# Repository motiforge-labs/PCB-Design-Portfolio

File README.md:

# PCB Design Portfolio – Fawaz

A collection of custom PCB projects designed in KiCad.

## Projects

* 🌈 RGB Mood Light PCB
* 🌤 ESP32 OLED Weather / System Display PCB
* ⌨️ ESP32 Macro Pad Pro PCB

Each project folder contains:

* KiCad source files
* PCB screenshots
* 3D renders
* Project documentation (PDF)

## 🌈 RGB Mood Light PCB

## 🌤 ESP32 OLED Weather Display PCB

## ⌨️ ESP32 Macro Pad Pro PCB

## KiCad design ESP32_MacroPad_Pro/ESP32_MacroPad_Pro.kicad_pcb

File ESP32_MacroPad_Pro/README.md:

## ⌨️ ESP32 Macro Pad Pro PCB

A compact 6-key programmable macro pad built around the Arduino Nano ESP32. The design integrates WS2812B RGB LEDs for per-key lighting, a 0.91-inch I²C OLED display for status and menu information, USB-C connectivity, and a dedicated reset button. The PCB was designed in KiCad with a focus on clean component placement, efficient routing, dual-layer ground planes, and successful ERC/DRC verification.

**Features**
- Arduino Nano ESP32
- 6 Mechanical Key Switches
- 6 × WS2812B RGB LEDs
- 0.91-inch I²C OLED Display
- USB-C Connectivity
- Dual-Layer PCB
- ERC: 0 Errors, 0 Warnings
- DRC: 0 Errors, 0 Warnings

## ⌨️ ESP32 Macro Pad Pro PCB

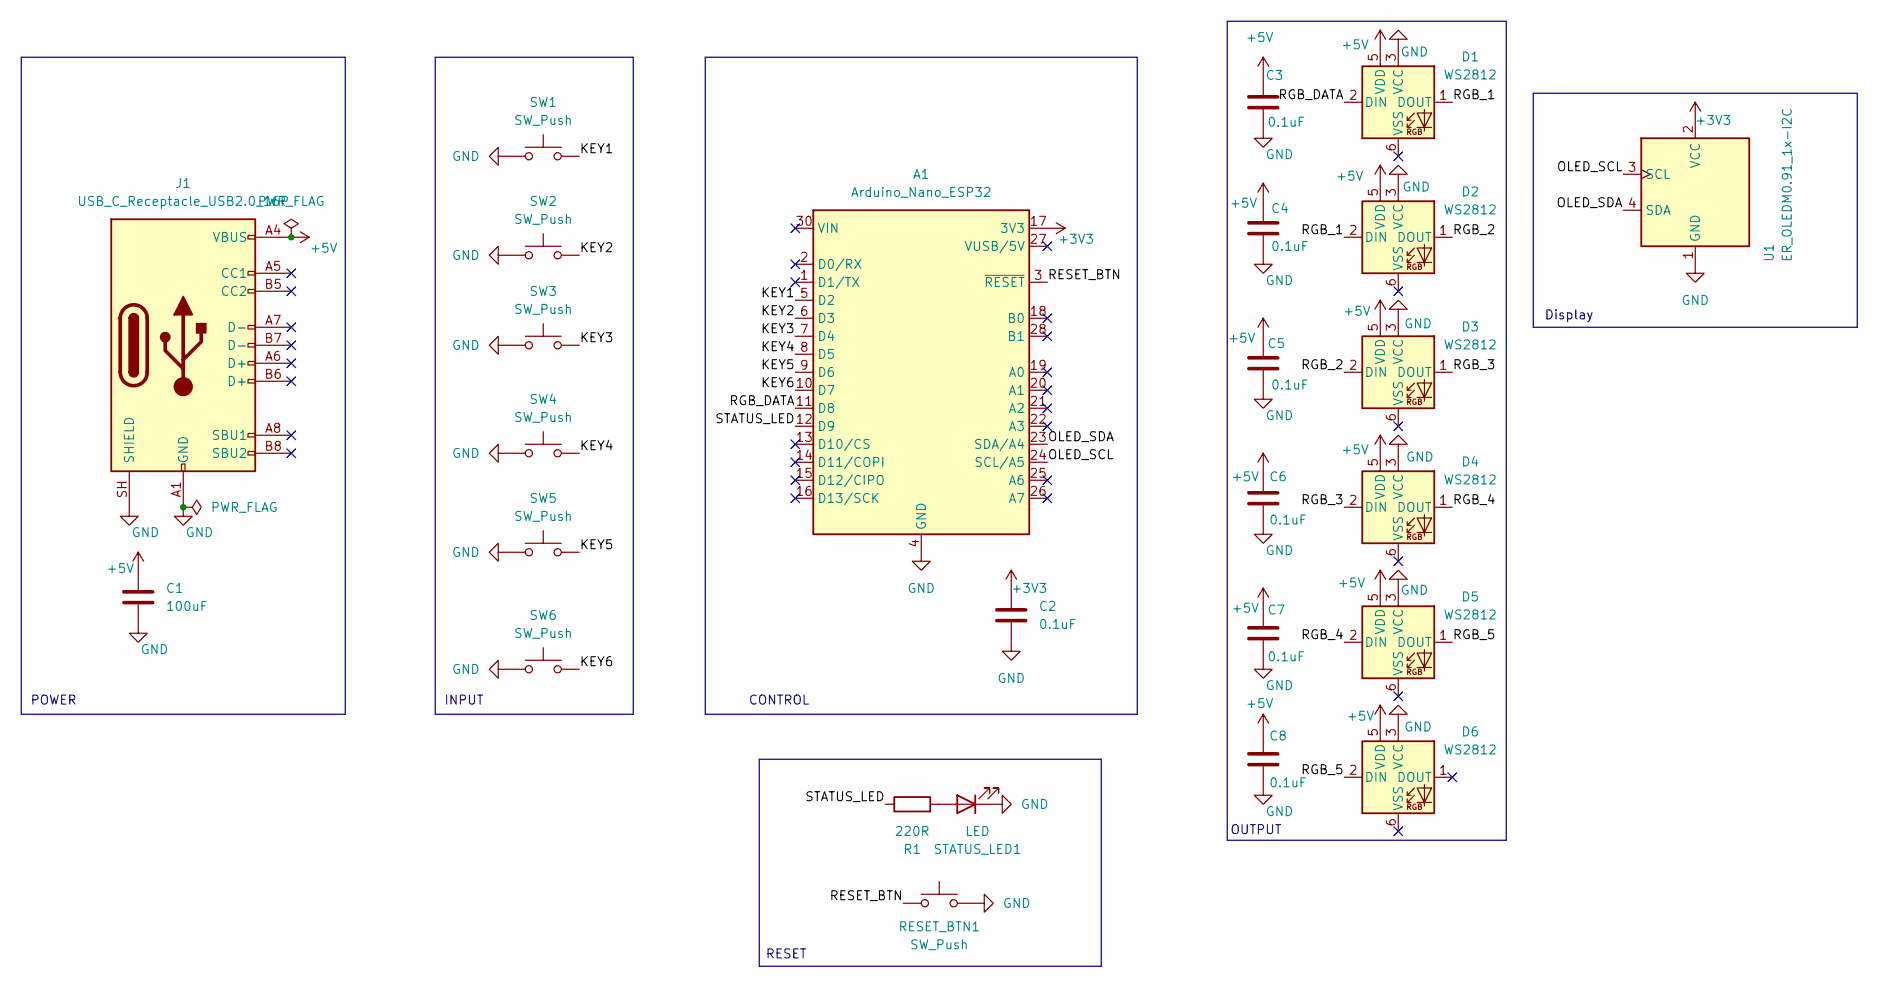
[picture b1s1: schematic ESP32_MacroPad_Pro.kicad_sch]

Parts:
A1: Arduino_Nano_ESP32; Arduino_Nano
C1: 100uF; C_1206_3216Metric
C2, C3, C4, C5, C6, C7, C8: 0.1uF; C_0805_2012Metric
D1, D2, D3, D4, D5, D6: WS2812; LED_WS2812_PLCC6_5.0x5.0mm_P1.6mm
J1: USB_C_Receptacle_USB2.0_16P; USB_C_Receptacle_HRO_TYPE-C-31-M-12
R1: 220R; R_0805_2012Metric
RESET_BTN1: SW_Push; SW_PUSH_6mm
STATUS_LED1: LED; LED_1206_3216Metric
SW1, SW2, SW3, SW4, SW5, SW6: SW_Push; SW_Cherry_MX_1.00u_PCB
U1: ER_OLEDM0.91_1x-I2C; FanPinHeader_1x04_P2.54mm_Vertical

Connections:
+3V3: A1.17 (3V3), C2.1, U1.2 (VCC)
+5V: C1.1, C3.1, C4.1, C5.1, C6.1, C7.1, C8.1, D1.5 (VDD), D2.5 (VDD), D3.5 (VDD), D4.5 (VDD), D5.5 (VDD), D6.5 (VDD), J1.A4 (VBUS), J1.A9 (VBUS), J1.B4 (VBUS), J1.B9 (VBUS)
/KEY1: A1.5 (D2), SW1.2
/KEY2: A1.6 (D3), SW2.2
/KEY3: A1.7 (D4), SW3.2
/KEY4: A1.8 (D5), SW4.2
/KEY5: A1.9 (D6), SW5.2
/KEY6: A1.10 (D7), SW6.2
/OLED_SCL: A1.24 (SCL/A5), U1.3 (SCL)
/OLED_SDA: A1.23 (SDA/A4), U1.4 (SDA)
/RESET_BTN: A1.3 (~RESET), RESET_BTN1.1
/RGB_1: D1.1 (DOUT), D2.2 (DIN)
/RGB_2: D2.1 (DOUT), D3.2 (DIN)
/RGB_3: D3.1 (DOUT), D4.2 (DIN)
/RGB_4: D4.1 (DOUT), D5.2 (DIN)
/RGB_5: D5.1 (DOUT), D6.2 (DIN)
/RGB_DATA: A1.11 (D8), D1.2 (DIN)
/STATUS_LED: A1.12 (D9), R1.1
GND: A1.4 (GND), A1.29 (GND), C1.2, C2.2, C3.2, C4.2, C5.2, C6.2, C7.2, C8.2, D1.3 (VCC), D2.3 (VCC), D3.3 (VCC), D4.3 (VCC), D5.3 (VCC), D6.3 (VCC), J1.A1 (GND), J1.A12 (GND), J1.B1 (GND), J1.B12 (GND), J1.SH (SHIELD), RESET_BTN1.2, STATUS_LED1.1 (K), SW1.1, SW2.1, SW3.1, SW4.1, SW5.1, SW6.1, U1.1 (GND)
unnamed: R1.2, STATUS_LED1.2 (A)

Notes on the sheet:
RESET
OUTPUT
POWER
Display
INPUT
CONTROL

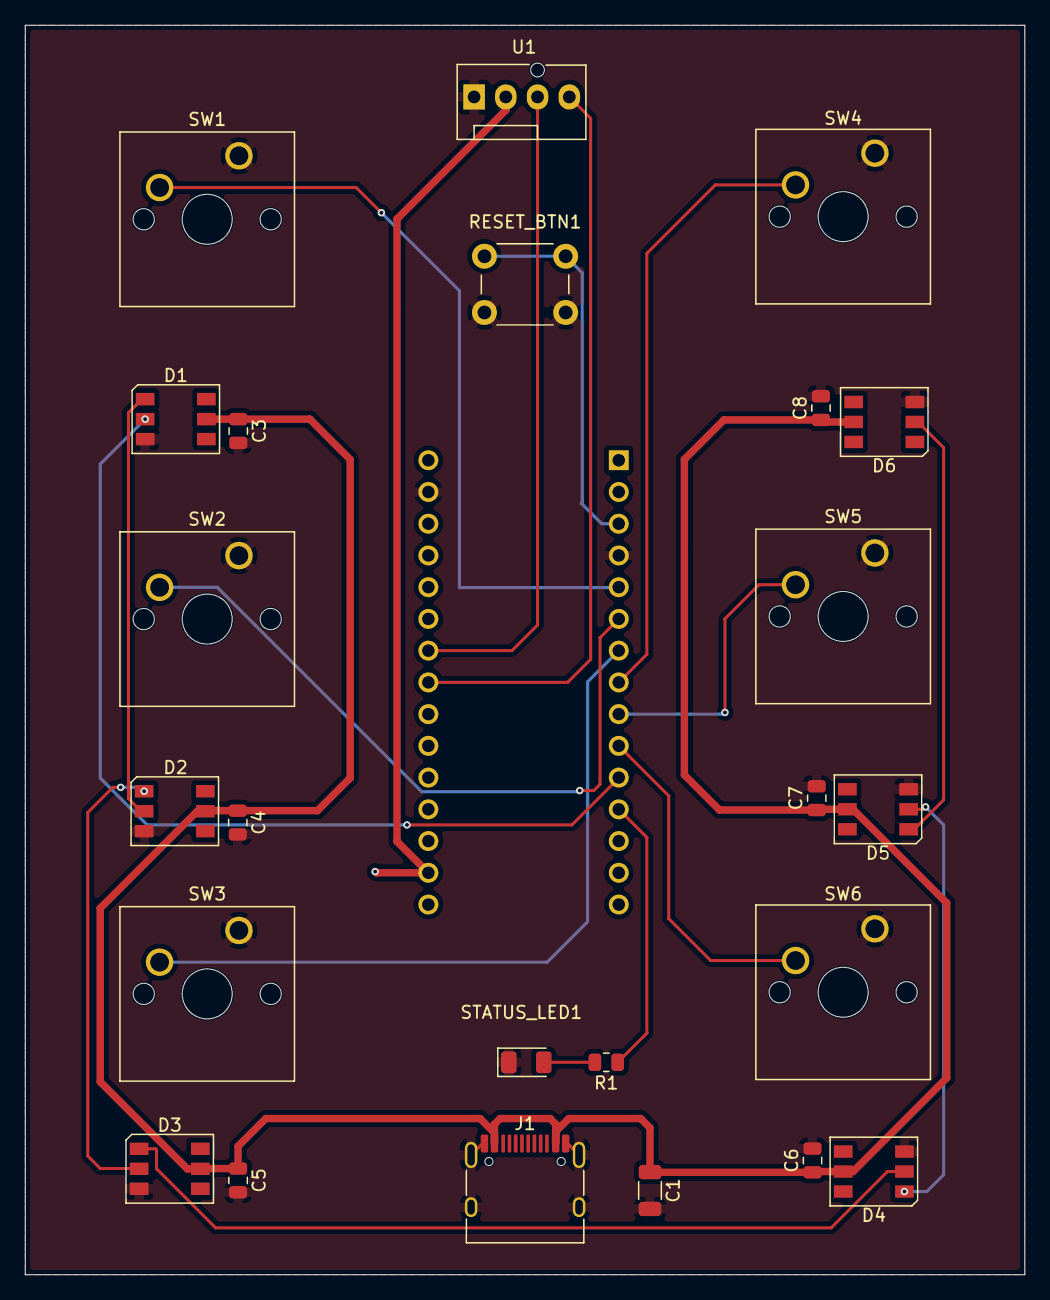
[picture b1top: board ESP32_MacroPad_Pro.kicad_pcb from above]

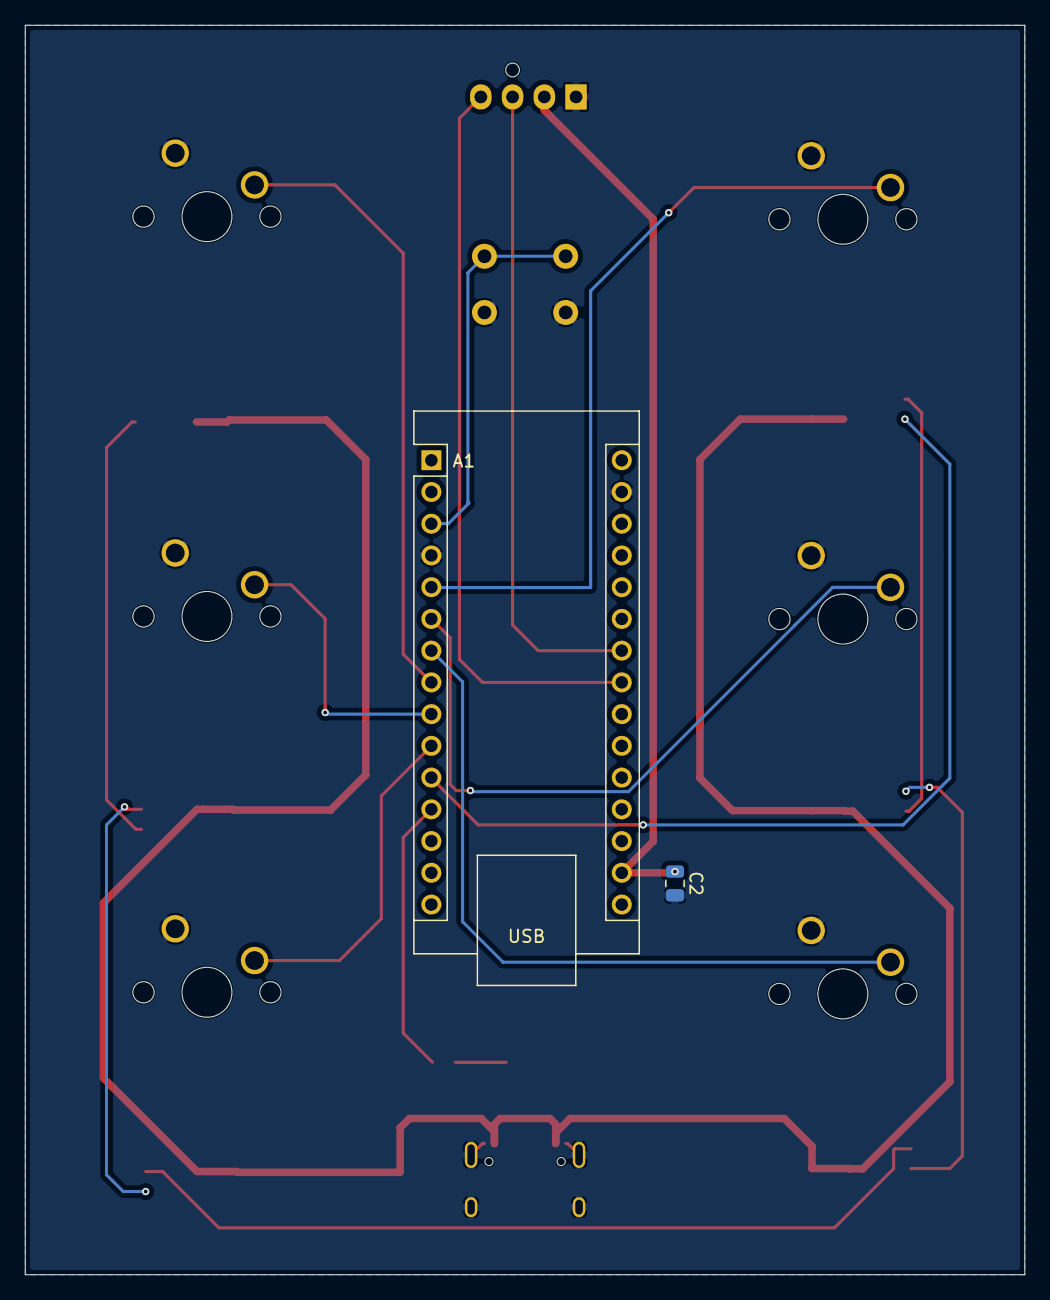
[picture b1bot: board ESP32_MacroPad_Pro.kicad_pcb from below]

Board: 2 copper layers, 80.0 x 100.0 mm, 26 parts (2 on the bottom side), 20 nets.

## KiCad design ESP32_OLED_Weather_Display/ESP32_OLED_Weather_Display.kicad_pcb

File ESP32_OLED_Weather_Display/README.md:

## 🌤 ESP32 OLED Weather / System Display PCB

A compact environmental monitoring and system display PCB built around the Arduino Nano ESP32. The board integrates a 0.91-inch I²C OLED display and a Bosch BME280 environmental sensor for measuring temperature, humidity, and atmospheric pressure. Designed in KiCad with an emphasis on clean routing, dual-layer ground planes, reliable I²C communication, and successful ERC/DRC verification.

**Features**
- Arduino Nano ESP32
- Bosch BME280 Environmental Sensor
- 0.91-inch I²C OLED Display
- USB-C Power Input
- Dual-Layer Ground Planes
- I²C Communication
- ERC: 0 Errors, 0 Warnings
- DRC: 0 Errors, 0 Warnings

## 🌤 ESP32 OLED Weather Display PCB

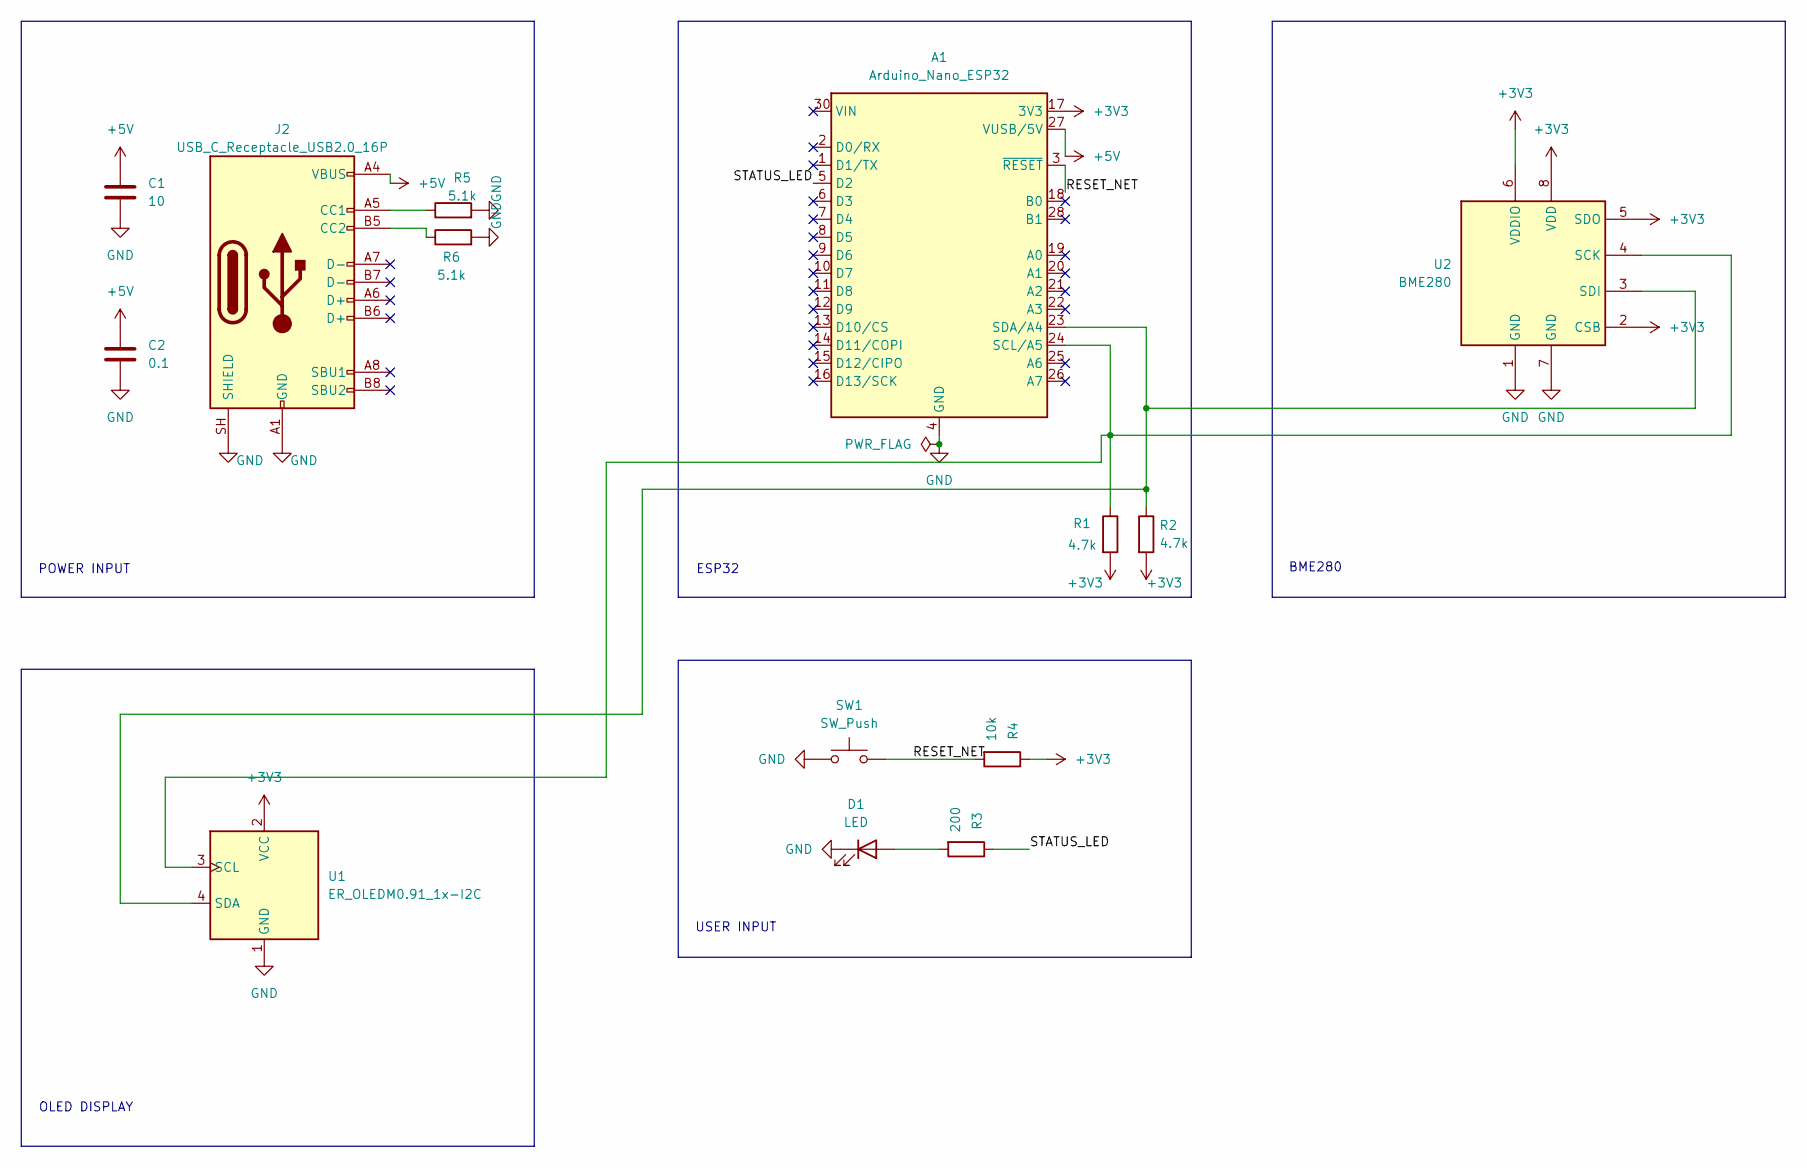
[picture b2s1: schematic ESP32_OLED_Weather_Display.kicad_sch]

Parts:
A1: Arduino_Nano_ESP32; Arduino_Nano
C1: 10; C_0805_2012Metric
C2: 0.1; C_0805_2012Metric
D1: LED; LED_0805_2012Metric
J2: USB_C_Receptacle_USB2.0_16P
R1, R2: 4.7k; R_0805_2012Metric
R3: 200; R_0805_2012Metric
R4: 10k; R_0805_2012Metric
R5, R6: 5.1k; R_0805_2012Metric
SW1: SW_Push; SW_PUSH_6mm
U1: ER_OLEDM0.91_1x-I2C
U2: BME280; Bosch_LGA-8_2.5x2.5mm_P0.65mm_ClockwisePinNumbering

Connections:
+3V3: A1.17 (3V3), R1.2, R2.2, R4.1, U1.2 (VCC), U2.2 (CSB), U2.5 (SDO), U2.6 (VDDIO), U2.8 (VDD)
+5V: A1.27 (VUSB/5V), C1.1, C2.1, J2.A4 (VBUS), J2.A9 (VBUS), J2.B4 (VBUS), J2.B9 (VBUS); also elsewhere on the board
/RESET_NET: A1.3 (~RESET), R4.2, SW1.2
/STATUS_LED: A1.5 (D2), R3.1
GND: A1.4 (GND), A1.29 (GND), C1.2, C2.2, D1.1 (K), J2.A1 (GND), J2.A12 (GND), J2.B1 (GND), J2.B12 (GND), J2.SH (SHIELD), R5.2, R6.2, SW1.1, U1.1 (GND), U2.1 (GND), U2.7 (GND); also elsewhere on the board
unnamed: A1.24 (SCL/A5), R1.1, U1.3 (SCL), U2.4 (SCK)
unnamed: A1.23 (SDA/A4), R2.1, U1.4 (SDA), U2.3 (SDI)
unnamed: D1.2 (A), R3.2
unnamed: J2.A5 (CC1), R5.1
unnamed: J2.B5 (CC2), R6.1

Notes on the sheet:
USER INPUT
OLED DISPLAY
ESP32
BME280
POWER INPUT

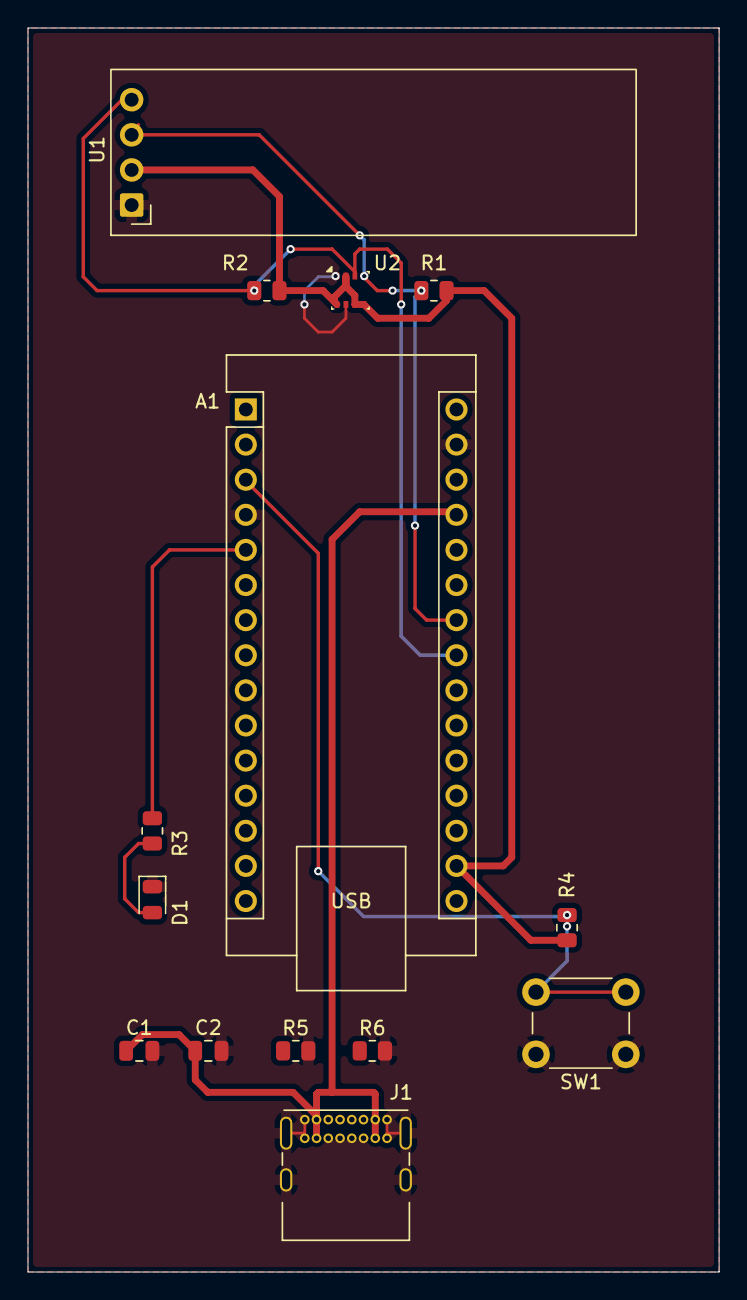
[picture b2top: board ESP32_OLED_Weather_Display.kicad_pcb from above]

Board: 2 copper layers, 50.0 x 90.0 mm, 14 parts (0 on the bottom side), 8 nets.

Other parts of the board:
J1: USB_C_Receptacle; USB_C_Receptacle_GCT_USB4085

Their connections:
+5V: J1.A4 (VBUS), J1.A9 (VBUS), J1.B4 (VBUS), J1.B9 (VBUS); also elsewhere on the board
GND: J1.A1 (GND), J1.A12 (GND), J1.B1 (GND), J1.B12 (GND), J1.SH (SHIELD); also elsewhere on the board

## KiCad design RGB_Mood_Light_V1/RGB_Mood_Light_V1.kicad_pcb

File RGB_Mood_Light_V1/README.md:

## 🌈 RGB Mood Light PCB

A compact RGB mood lighting PCB built around the Arduino Nano ESP32. The board drives multiple WS2812B addressable RGB LEDs while being powered through USB-C. Designed in KiCad, the project demonstrates clean schematic design, efficient PCB routing, proper power distribution, and successful ERC/DRC verification.

**Features**
- Arduino Nano ESP32
- WS2812B Addressable RGB LEDs
- USB-C Power Input
- Dual-Layer PCB
- Clean Power Distribution
- ERC: 0 Errors, 0 Warnings
- DRC: 0 Errors, 0 Warnings

## 🌈 RGB Mood Light PCB

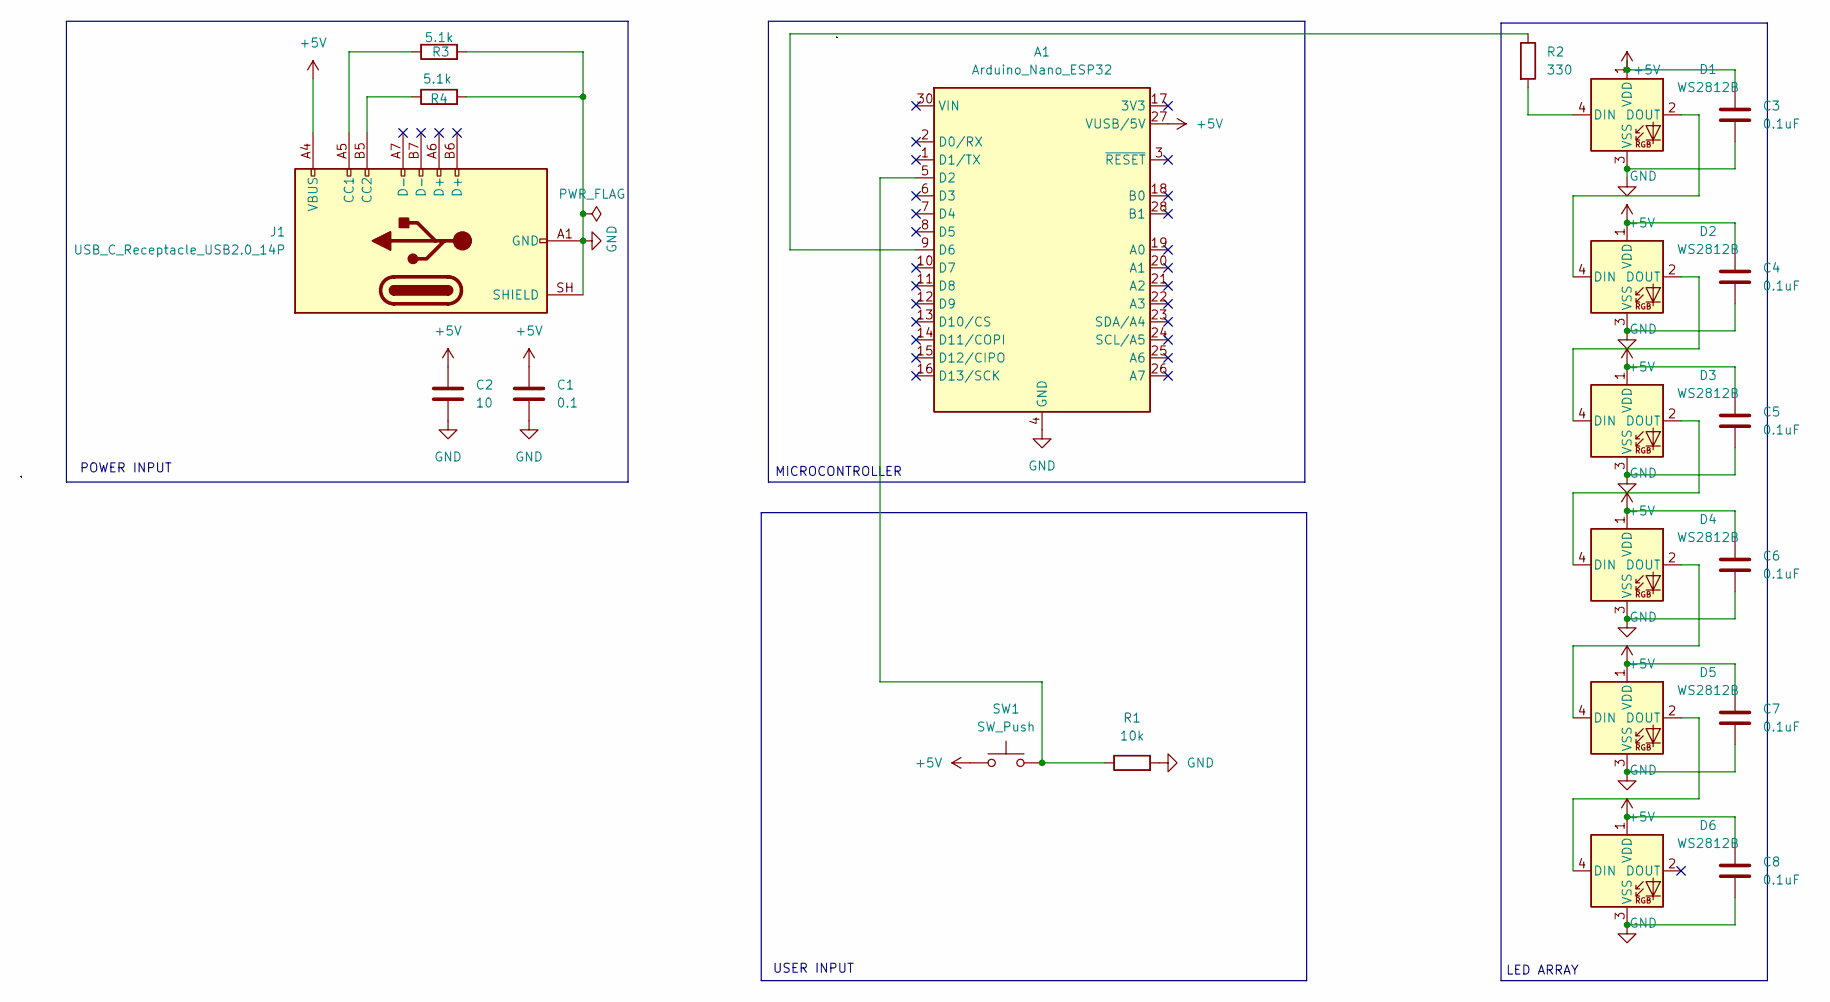
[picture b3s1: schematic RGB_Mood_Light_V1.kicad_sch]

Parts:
A1: Arduino_Nano_ESP32; Arduino_Nano
C1: 0.1; C_0805_2012Metric
C2: 10; C_0805_2012Metric
C3, C4, C5, C6, C7, C8: 0.1uF; C_0805_2012Metric
D1, D2, D3, D4, D5, D6: WS2812B; LED_WS2812B_PLCC4_5.0x5.0mm_P3.2mm
J1: USB_C_Receptacle_USB2.0_14P
R1: 10k; R_0805_2012Metric
R2: 330; R_0805_2012Metric
R3, R4: 5.1k; R_0805_2012Metric
SW1: SW_Push; SW_PUSH_6mm

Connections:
+5V: A1.27 (VUSB/5V), C1.1, C2.1, C3.1, C4.1, C5.1, C6.1, C7.1, C8.1, D1.1 (VDD), D2.1 (VDD), D3.1 (VDD), D4.1 (VDD), D5.1 (VDD), D6.1 (VDD), J1.A4 (VBUS), J1.A9 (VBUS), J1.B4 (VBUS), J1.B9 (VBUS), SW1.1
GND: A1.4 (GND), A1.29 (GND), C1.2, C2.2, C3.2, C4.2, C5.2, C6.2, C7.2, C8.2, D1.3 (VSS), D2.3 (VSS), D3.3 (VSS), D4.3 (VSS), D5.3 (VSS), D6.3 (VSS), J1.A1 (GND), J1.A12 (GND), J1.B1 (GND), J1.B12 (GND), J1.SH (SHIELD), R1.2, R3.2, R4.2
unnamed: A1.5 (D2), R1.1, SW1.2
unnamed: A1.9 (D6), R2.1
unnamed: D1.4 (DIN), R2.2
unnamed: D1.2 (DOUT), D2.4 (DIN)
unnamed: D2.2 (DOUT), D3.4 (DIN)
unnamed: D3.2 (DOUT), D4.4 (DIN)
unnamed: D4.2 (DOUT), D5.4 (DIN)
unnamed: D5.2 (DOUT), D6.4 (DIN)
unnamed: J1.A5 (CC1), R3.1
unnamed: J1.B5 (CC2), R4.1

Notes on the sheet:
LED ARRAY
USER INPUT
MICROCONTROLLER
POWER INPUT

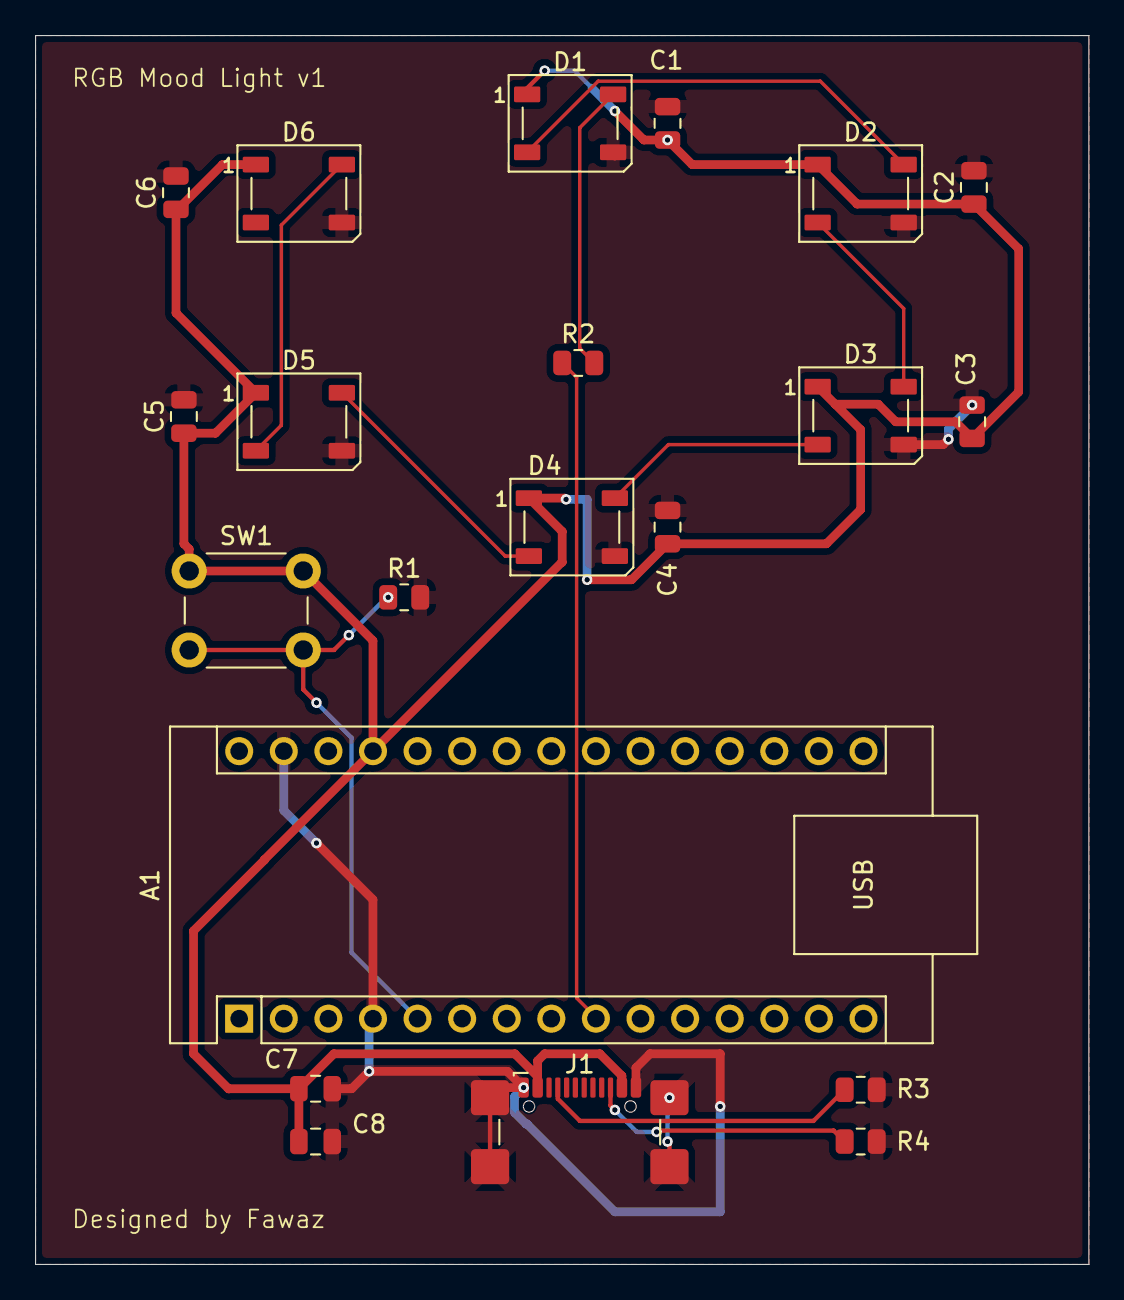
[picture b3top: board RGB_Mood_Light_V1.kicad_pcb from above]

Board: 2 copper layers, 60.0 x 70.0 mm, 21 parts (0 on the bottom side), 12 nets.
